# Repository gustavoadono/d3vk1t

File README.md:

# **d3vkit board**
This repository contains information and resources related to a custom board featuring the STM32F412RET6 microcontroller. This board has been developed for study purposes and includes several integrated components, such as the LSM6DSMTR sensor (accelerometer and gyroscope), the HDC1080DMBR sensor (temperature and humidity), and the LPS22HBTR sensor (barometer). Additionally, the board features an SD card slot, CAN and RS485 interfaces, USB connectivity, and the ESP32-C3-WROOM-02-H4 module for Wi-Fi and Bluetooth communication.

# **overview**

The custom board has been designed to provide a flexible platform for studying and experimentation using the STM32F412RET6 microcontroller. It encompasses the following key features:

1. **STM32F412RET6 Microcontroller**: The STM32F412RET6 is a high-performance microcontroller based on the ARM Cortex-M4 architecture. It operates at a clock frequency of up to 100 MHz, with 512 KB of flash memory and 128 KB of RAM. This microcontroller offers advanced features, including peripheral interfaces, ADC, timers, and serial communication.

2. **LSM6DSMTR Sensor (Accelerometer and Gyroscope)**: The board integrates the LSM6DSMTR sensor, which combines a three-axis accelerometer and a three-axis gyroscope. This enables accurate motion detection, acceleration measurement, and inclination sensing.

3. **HDC1080DMBR Sensor (Temperature and Humidity)**: The board includes the HDC1080DMBR sensor, which provides precise temperature and humidity measurements in the surrounding environment. This feature is beneficial for projects involving climate monitoring or environmental control.

4. **LPS22HBTR Sensor (Barometer)**: The board incorporates the LPS22HBTR sensor, allowing atmospheric pressure measurements. This functionality proves useful for projects related to weather monitoring, altitude sensing, or flight control.

5. **SD Card Slot**: The board features an SD card slot, enabling read and write operations with removable memory cards. This facilitates data storage, such as measurement logs or configuration files.

6. **CAN and RS485 Interfaces**: The board incorporates circuits for CAN and RS485 interfaces, widely used in industrial applications for device communication. These interfaces ease integration within automation systems.

7. **USB Connectivity**: The board provides a USB port for communication with a computer or connection to other USB devices. This port supports data transfer and can power the board.

8. **ESP32-C3-WROOM-02-H4 Module (Wi-Fi and Bluetooth)**: The board includes the ESP32-C3-WROOM-02-H4 module, offering Wi-Fi and Bluetooth connectivity. This enables wireless communication, connection to Wi-Fi networks, and interaction with Bluetooth devices, making it suitable for IoT projects.

# **contact**

If you have any questions or need further information, feel free to get in touch. You can reach me via the provided email address in the repository's profile.

# bill of material

you can see the entire bill of materials through this link [d3vk1t-bom](https://gustavoadono.github.io/board/d3vk1t-bom).

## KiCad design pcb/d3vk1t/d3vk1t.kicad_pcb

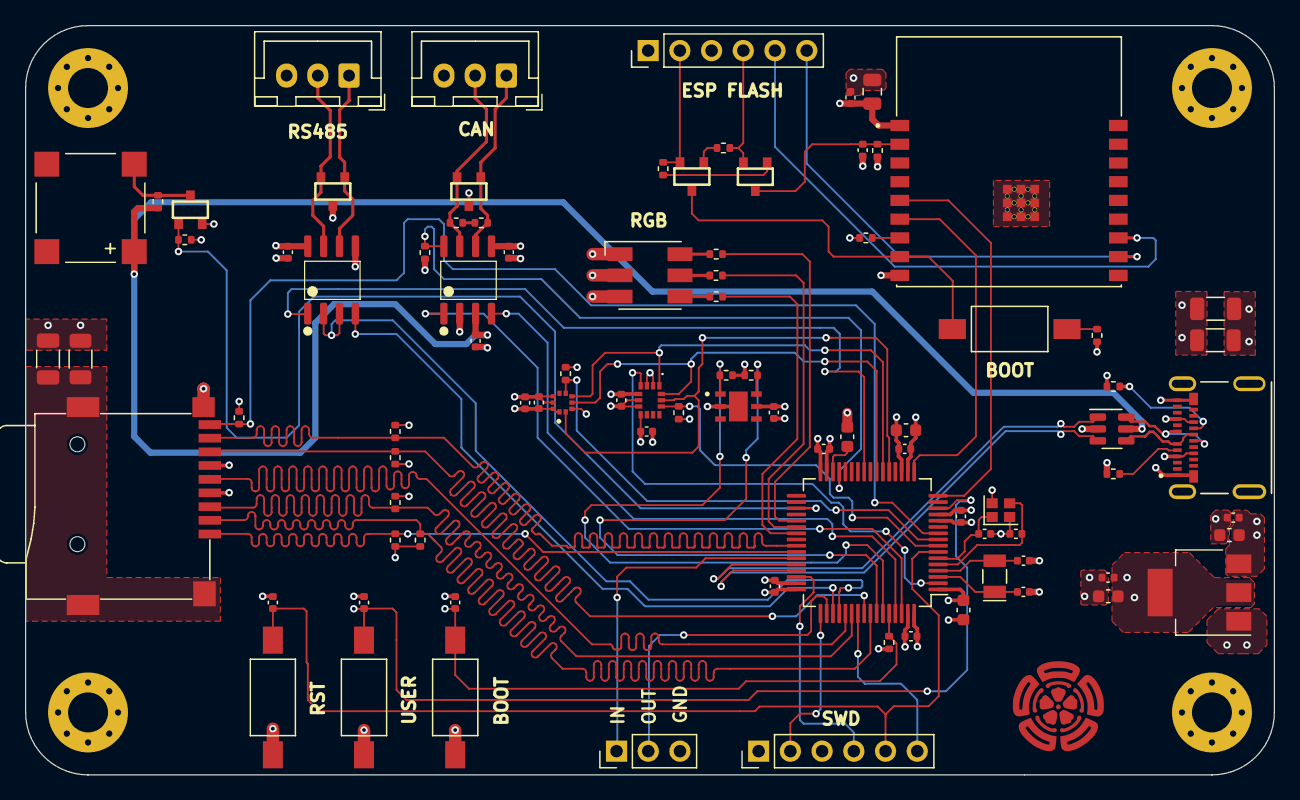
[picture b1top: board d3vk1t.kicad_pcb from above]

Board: 4 copper layers, 100.0 x 60.0 mm, 93 parts (0 on the bottom side), 70 nets.

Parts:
BZ1: Buzzer; PUIAudio_SMT_0825_S_4_R
C1, C2, C3, C4, C5, C9, C10, C12, C15, C16, C17, C18, C19, C20, C21, C23, C25, C26, C27, C32: 100nF; C_0402_1005Metric
C6, C22, C24: 1uF; C_0603_1608Metric
C7: 4.7uF; C_0603_1608Metric
C8: 2.2uF; C_0603_1608Metric
C11: 22uF; C_0805_2012Metric
C13, C14: 1nF; C_1206_3216Metric
C28, C29: 20pF; C_0402_1005Metric
C30, C31: 6.8pF; C_0402_1005Metric
D1: LED_RGB; LED_RGB_5050-6
D2: PESD2CAN_215; SOT-23B
D4: SM712-02HTG; SOT-23B
H1, H2, H3, H4: MountingHole; MountingHole_3.2mm_M3_Pad_Via
IC1: STM32F412RET6; LQFP-64_10x10mm_P0.5mm
IC2: LSM6DSMTR; PQFN50P300X250X86-14N
IC3: HDC1080DMBR; SON100P300X300X80-7N
IC4: LPS22HBTR; PQFN50P200X200X80-10N
IC5: TJA1042T/3/1J; SOIC127P600X175-8N
IC6: MAX3485CSA+T; SOIC127P600X175-8N
IC7: USBLC6-2SC6; SOT-23-6
IC8: LM1117MP-3.3; SOT-223-3_TabPin2
J1: Conn_01x03; PinHeader_1x03_P2.54mm_Vertical
J2, J3: Conn_01x06; PinHeader_1x06_P2.54mm_Vertical
J4, J5: Conn_01x03; JST_XH_B3B-XH-A_1x03_P2.50mm_Vertical
Q1, Q2: MMBT2222; SOT-23B
Q3: 2N7002; SOT-23B
R1, R2, R3, R4, R5, R10, R11, R12, R13, R14, R15, R16, R25: 10K; R_0402_1005Metric
R6, R9: 1M; R_1206_3216Metric
R7, R8: 5.1K; R_0402_1005Metric
R17: 1K; R_0402_1005Metric
R18: 330R; R_0402_1005Metric
R19: 470R; R_0402_1005Metric
R20, R21: 120R; R_0402_1005Metric
R22: 0R; R_0402_1005Metric
R23, R24, R26, R27, R28: 47K; R_0402_1005Metric
SW1, SW2, SW3, SW4: SW_Push; SW_SPST_FSMSM
U1: ESP32-C3-WROOM-02-H4; MODULE_ESP32-C3-WROOM-02-H4
X1: 105450-0101; MOLEX_105450-0101
X2: Micro_SD_Card_Det; microSD_SOFNG_TF-015
Y1: 32.7680KHZ; Crystal_SMD_EuroQuartz_EQ161-2Pin_3.2x1.5mm
Y2: 24MHz; Crystal_SMD_2016-4Pin_2.0x1.6mm

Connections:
+3.3V: C1.1, C2.1, C3.1, C4.1, C5.1, C6.1, C7.1, C10.1, C11.1, C16.1, C17.1, C18.1, C19.1, C21.1, C23.1, C24.1, C26.2, C27.2, C32.2, IC1.1 (VBAT), IC1.13 (VDDA), IC1.19 (VDD), IC1.32 (VDD), IC1.48 (VDD), IC1.64 (VDD), IC2.5 (VDDIO), IC2.8 (VDD), IC3.5 (VDD), IC4.1 (VDD_IO), IC4.10 (VDD), IC5.5 (VIO), IC6.8 (VCC), IC8.2 (VO), J2.1, J3.1, R3.2, R5.2, R10.2, R11.2, R12.2, R13.2, R15.2, R23.2, R24.2, R26.2, R27.2, R28.2, SW4.1, U1.1 (3V3), X2.4 (VDD)
+5V: BZ1.1 (-), C20.1, C22.1, C25.2, IC5.3 (VCC), IC7.5 (VBUS), IC8.3 (VI), R17.2, X1.A4 (VBUS_A), X1.A9 (VBUS_A), X1.B4 (VBUS_B), X1.B9 (VBUS_B)
/comm/CAN1_RX: IC1.61 (PB8), IC5.4 (RXD)
/comm/CAN1_TX: IC1.62 (PB9), IC5.1 (TXD)
/comm/CAN_H: D2.1 (C1), IC5.6 (CANL), J4.1, R22.2
/comm/CAN_L: D2.2 (C2), IC5.7 (CANH), J4.2, R21.1
/comm/CAN_STB: IC1.29 (PB10), IC5.8 (STB), R14.2
/comm/RS485_A: D4.2 (A2), IC6.7 (B), J5.2
/comm/RS485_B: D4.1 (A1), IC6.6 (A), J5.1
/comm/RS485_DE: IC1.52 (PC11), IC6.2 (~RE), IC6.3 (DE)
/mcu/BOOT0: C32.1, IC1.60 (BOOT0), R25.2, SW4.2
/mcu/BUZZER: IC1.35 (PB14), Q3.1 (G), R16.2
/mcu/NRST: C9.1, IC1.7 (NRST), J2.5, SW2.2
/mcu/OSC32_IN: C30.1, IC1.3 (PC14), Y1.1
/mcu/OSC32_OUT: C31.1, IC1.4 (PC15), Y1.2
/mcu/OSC_IN: C28.1, IC1.5 (PH0), Y2.3
/mcu/OSC_OUT: C29.1, IC1.6 (PH1), Y2.1
/mcu/RGB_B: IC1.39 (PC8), R20.2
/mcu/RGB_G: IC1.38 (PC7), R19.2
/mcu/RGB_R: IC1.37 (PC6), R18.2
/mcu/SDIO_CLK: IC1.53 (PC12), X2.5 (CLK)
/mcu/SDIO_CMD: IC1.54 (PD2), R24.1, X2.3 (CMD)
/mcu/SDIO_D0: IC1.56 (PB4), R26.1, X2.7 (DAT0)
/mcu/SDIO_D1: IC1.41 (PA8), R27.1, X2.8 (DAT1)
/mcu/SDIO_D2: IC1.42 (PA9), R28.1, X2.1 (DAT2)
/mcu/SDIO_D3: IC1.57 (PB5), R23.1, X2.2 (DAT3/CD)
/mcu/SDIO_DET: IC1.10 (PC2), R15.1, X2.10 (DET_A)
/mcu/SWCLK: IC1.49 (PA14), J2.2
/mcu/SWDIO: IC1.46 (PA13), J2.4
/mcu/SWO: IC1.55 (PB3), J2.6
/mcu/USART1_RX: IC1.43 (PA10), J1.1
/mcu/USART1_TX: IC1.50 (PA15), J1.2
/mcu/USART2_RX: IC1.17 (PA3), U1.6 (IO7)
/mcu/USART2_TX: IC1.16 (PA2), U1.5 (IO6)
/mcu/USART3_RX: IC1.25 (PC5), IC6.1 (RO)
/mcu/USART3_TX: IC1.51 (PC10), IC6.4 (DI)
/mcu/USB_N: IC1.44 (PA11), IC7.1 (I/O1)
/mcu/USB_P: IC1.45 (PA12), IC7.3 (I/O2)
/mcu/USER: C15.1, IC1.14 (PA0), SW3.2
/sensors/ACC_CS: IC1.8 (PC0), IC2.12 (CS), R10.1
/sensors/ACC_INT: IC1.2 (PC13), IC2.4 (INT1)
/sensors/BARO_CS: IC1.9 (PC1), IC4.6 (CS), R11.1
/sensors/I2C1_SCL: IC1.58 (PB6), IC3.6 (SCL), R12.1
/sensors/I2C1_SDA: IC1.59 (PB7), IC3.1 (SDA), R13.1
/sensors/SPI1_CLK: IC1.21 (PA5), IC2.13 (SCL/SPC), IC4.2 (SCL/SPC)
/sensors/SPI1_MISO: IC1.22 (PA6), IC2.1 (SDO/SA0), IC4.5 (SDO/SA0)
/sensors/SPI1_MOSI: IC1.23 (PA7), IC2.14 (SDA/SDI/SDO), IC4.4 (SDA/SDI/SDO)
/usb/USB_CON_N: IC7.6 (I/O1), X1.A7 (D1-), X1.B7 (D2-)
/usb/USB_CON_P: IC7.4 (I/O2), X1.A6 (D1+), X1.B6 (D2+)
/wifi_ble/DTR: J3.2, Q2.2, R1.1
/wifi_ble/ESP_RX: J3.6, U1.11 (RXD)
/wifi_ble/ESP_TX: J3.5, U1.12 (TXD)
/wifi_ble/GPIO8: R5.1, U1.7 (IO8)
/wifi_ble/GPIO9: Q2.3, SW1.1, U1.8 (IO9)
/wifi_ble/RESET: C12.1, Q1.3, R3.1, U1.2 (EN)
/wifi_ble/RTS: J3.4, Q1.2, R2.1
GND: C1.2, C2.2, C3.2, C4.2, C5.2, C6.2, C7.2, C8.2, C9.2, C10.2, C11.2, C12.2, C13.2, C14.2, C15.2, C16.2, C17.2, C18.2, C19.2, C20.2, C21.2, C22.2, C23.2, C24.2, C25.1, C26.1, C27.1, C28.2, C29.2, C30.2, C31.2, D1.1 (RK), D1.2 (GK), D1.3 (BK), D2.3 (C3), D4.3 (common), IC1.12 (VSSA), IC1.18 (VSS), IC1.31 (VSS), IC1.47 (VSS), IC1.63 (VSS), IC2.2 (SDX), IC2.3 (SCX), IC2.6 (GND), IC2.7 (GND), IC3.2 (GND), IC3.7 (EXP), IC4.3 (RESERVED), IC4.8 (GND), IC4.9 (GND), IC5.2 (GND), IC6.5 (GND), IC7.2 (GND), IC8.1 (GND), J1.3, J2.3, J3.3, J4.3, J5.3, Q3.2 (S), R4.2, R6.1, R7.1, R8.1, R9.1, R14.1, R16.1, R25.1, SW2.1, SW3.1, U1.9 (GND), U1.19 (GND), U1.20 (GND), U1.21 (GND), U1.22 (GND), U1.23 (GND), U1.24 (GND), U1.25 (GND), U1.26 (GND), U1.27 (GND), U1.28 (GND), U1.29 (GND), U1.30 (GND), U1.31 (GND), U1.32 (GND), U1.33 (GND), U1.34 (GND), U1.35 (GND), U1.36 (GND), U1.37 (GND), U1.38 (GND), U1.39 (GND), X1.A1 (GND_A), X1.A12 (GND_A), X1.B1 (GND_B), X1.B12 (GND_B), X2.6 (VSS), X2.9 (DET_B), Y2.2, Y2.4
unnamed: BZ1.2 (+), Q3.3 (D), R17.1
unnamed: C13.1, R6.2, X1.S1 (SHIELD), X1.S2 (SHIELD), X1.S3 (SHIELD), X1.S4 (SHIELD)
unnamed: D1.4 (BA), R20.1
unnamed: D1.5 (GA), R19.1
unnamed: D1.6 (RA), R18.1
unnamed: C8.1, IC1.30 (VCAP_1)
unnamed: Q1.1, R1.2
unnamed: Q2.1, R2.2
unnamed: R4.1, SW1.2
unnamed: R21.2, R22.1
unnamed: R8.2, X1.A5 (CC1)
unnamed: R7.2, X1.B5 (CC2)
unnamed: C14.1, R9.2, X2.11 (SHIELD)

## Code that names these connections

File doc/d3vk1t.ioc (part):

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Mcu.Name=STM32F412R(E-G)Tx
Mcu.Package=LQFP64
Mcu.UserName=STM32F412RETx
PA0.GPIOParameters=GPIO_Label
PA0.GPIO_Label=USER_BTN
PA0.Signal=GPXTI0
PA10.Mode=Asynchronous
PA10.Signal=USART1_RX
PA11.Mode=Device_Only
PA11.Signal=USB_OTG_FS_DM
PA12.Mode=Device_Only
PA12.Signal=USB_OTG_FS_DP
PA13.Mode=Trace_Asynchronous_SW
PA13.Signal=SYS_JTMS-SWDIO
PA14.Mode=Trace_Asynchronous_SW
PA14.Signal=SYS_JTCK-SWCLK
PA15.Mode=Asynchronous
PA15.Signal=USART1_TX
PA2.Mode=Asynchronous
PA2.Signal=USART2_TX
PA3.Mode=Asynchronous
PA3.Signal=USART2_RX
PA5.Mode=Full_Duplex_Master
PA5.Signal=SPI1_SCK
PA6.Mode=Full_Duplex_Master
PA6.Signal=SPI1_MISO
PA7.Mode=Full_Duplex_Master
PA7.Signal=SPI1_MOSI
PA8.Mode=SD_4_bits_Wide_bus
PA8.Signal=SDIO_D1
PA9.Mode=SD_4_bits_Wide_bus
PA9.Signal=SDIO_D2
PB10.GPIOParameters=GPIO_Label
PB10.GPIO_Label=CAN_STB
PB10.Signal=GPIO_Output
PB14.GPIOParameters=GPIO_Label
PB14.GPIO_Label=BUZZER
PB14.Signal=S_TIM12_CH1
PB3.Mode=Trace_Asynchronous_SW
PB3.Signal=SYS_JTDO-SWO
PB4.Mode=SD_4_bits_Wide_bus
PB4.Signal=SDIO_D0
PB5.Mode=SD_4_bits_Wide_bus
PB5.Signal=SDIO_D3
PB6.Mode=I2C
PB6.Signal=I2C1_SCL
PB7.Mode=I2C
PB7.Signal=I2C1_SDA
PB8.Mode=CAN_Activate
PB8.Signal=CAN1_RX
PB9.Mode=CAN_Activate
PB9.Signal=CAN1_TX
PC0.GPIOParameters=GPIO_Label
PC0.GPIO_Label=ACC_CS
PC0.Signal=GPIO_Output
PC1.GPIOParameters=GPIO_Label
PC1.GPIO_Label=BARO_CS
PC1.Signal=GPIO_Output
PC10.Mode=Asynchronous
PC10.Signal=USART3_TX
PC11.GPIOParameters=GPIO_Label
PC11.GPIO_Label=RS485_DE
PC11.Signal=GPIO_Output
PC12.Mode=SD_4_bits_Wide_bus
PC12.Signal=SDIO_CK
PC13.GPIOParameters=GPIO_Label
PC13.GPIO_Label=ACC_INT
PC13.Signal=GPXTI13
PC14-OSC32_IN.Mode=LSE-External-Oscillator
PC14-OSC32_IN.Signal=RCC_OSC32_IN
PC15-OSC32_OUT.Mode=LSE-External-Oscillator
PC15-OSC32_OUT.Signal=RCC_OSC32_OUT
PC2.GPIOParameters=GPIO_Label
PC2.GPIO_Label=SD_DET
PC2.Signal=GPXTI2
PC5.Mode=Asynchronous
PC5.Signal=USART3_RX
PC6.GPIOParameters=GPIO_Label
PC6.GPIO_Label=RGB_RED
PC6.Signal=S_TIM8_CH1
PC7.GPIOParameters=GPIO_Label
PC7.GPIO_Label=RGB_GREEN
PC7.Signal=S_TIM8_CH2
PC8.GPIOParameters=GPIO_Label
PC8.GPIO_Label=RGB_BLUE
PC8.Signal=S_TIM8_CH3
PD2.Mode=SD_4_bits_Wide_bus
PD2.Signal=SDIO_CMD
PH0\ -\ OSC_IN.Mode=HSE-External-Oscillator
PH0\ -\ OSC_IN.Signal=RCC_OSC_IN
PH1\ -\ OSC_OUT.Mode=HSE-External-Oscillator
PH1\ -\ OSC_OUT.Signal=RCC_OSC_OUT
RCC.HSE_VALUE=24000000
RCC.SYSCLKFreq_VALUE=72000000
RCC.SYSCLKSource=RCC_SYSCLKSOURCE_PLLCLK
board=custom

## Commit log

2023-04-03 [project update] - added template folders. - added block diagram.
2023-04-12 [pcb: define board shape]
2023-04-13 [doc: update mcu pinout, pcb: update board shape]
2023-04-14 doc: added f4 hw dev doc
2023-04-26 [update all schematics sheets]
2023-05-05 sch: update all sch sheets.
2023-05-16 pcb: update layout
2023-05-22 project update - update pcb layout. - update schmatics sheets. - added manufacturing files. - added documentation files.
2023-05-22 update documentation
2023-05-23 added interactive bom link
2023-05-23 added block diagram
2023-05-23 update a high quality block diagram:
